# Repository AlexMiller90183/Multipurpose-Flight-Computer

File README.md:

Multipurpose Flight Computer
============================
This project is a flight computer designed to be used for many purposes, whether it be RC airplanes, model rockets, or even drones. Because of the broad usage capability it's designed to be as small as possible. It includes a barometer, IMU, servo outputs, and a battery controller. It is all powered by the STM32

PCB:
====
Schematic:

Why this?
=========
Well there I was... sitting bored at home

Just kidding. I previously made an Arduino Nano based flight computer with premade components and it was my first ever PCB! As I've learned more though, I wanted to challenge myself with something a little more complex and this was the perfect idea! I followed @NotARoomba's tutorial, but tried to make my version as small and compact as possible.

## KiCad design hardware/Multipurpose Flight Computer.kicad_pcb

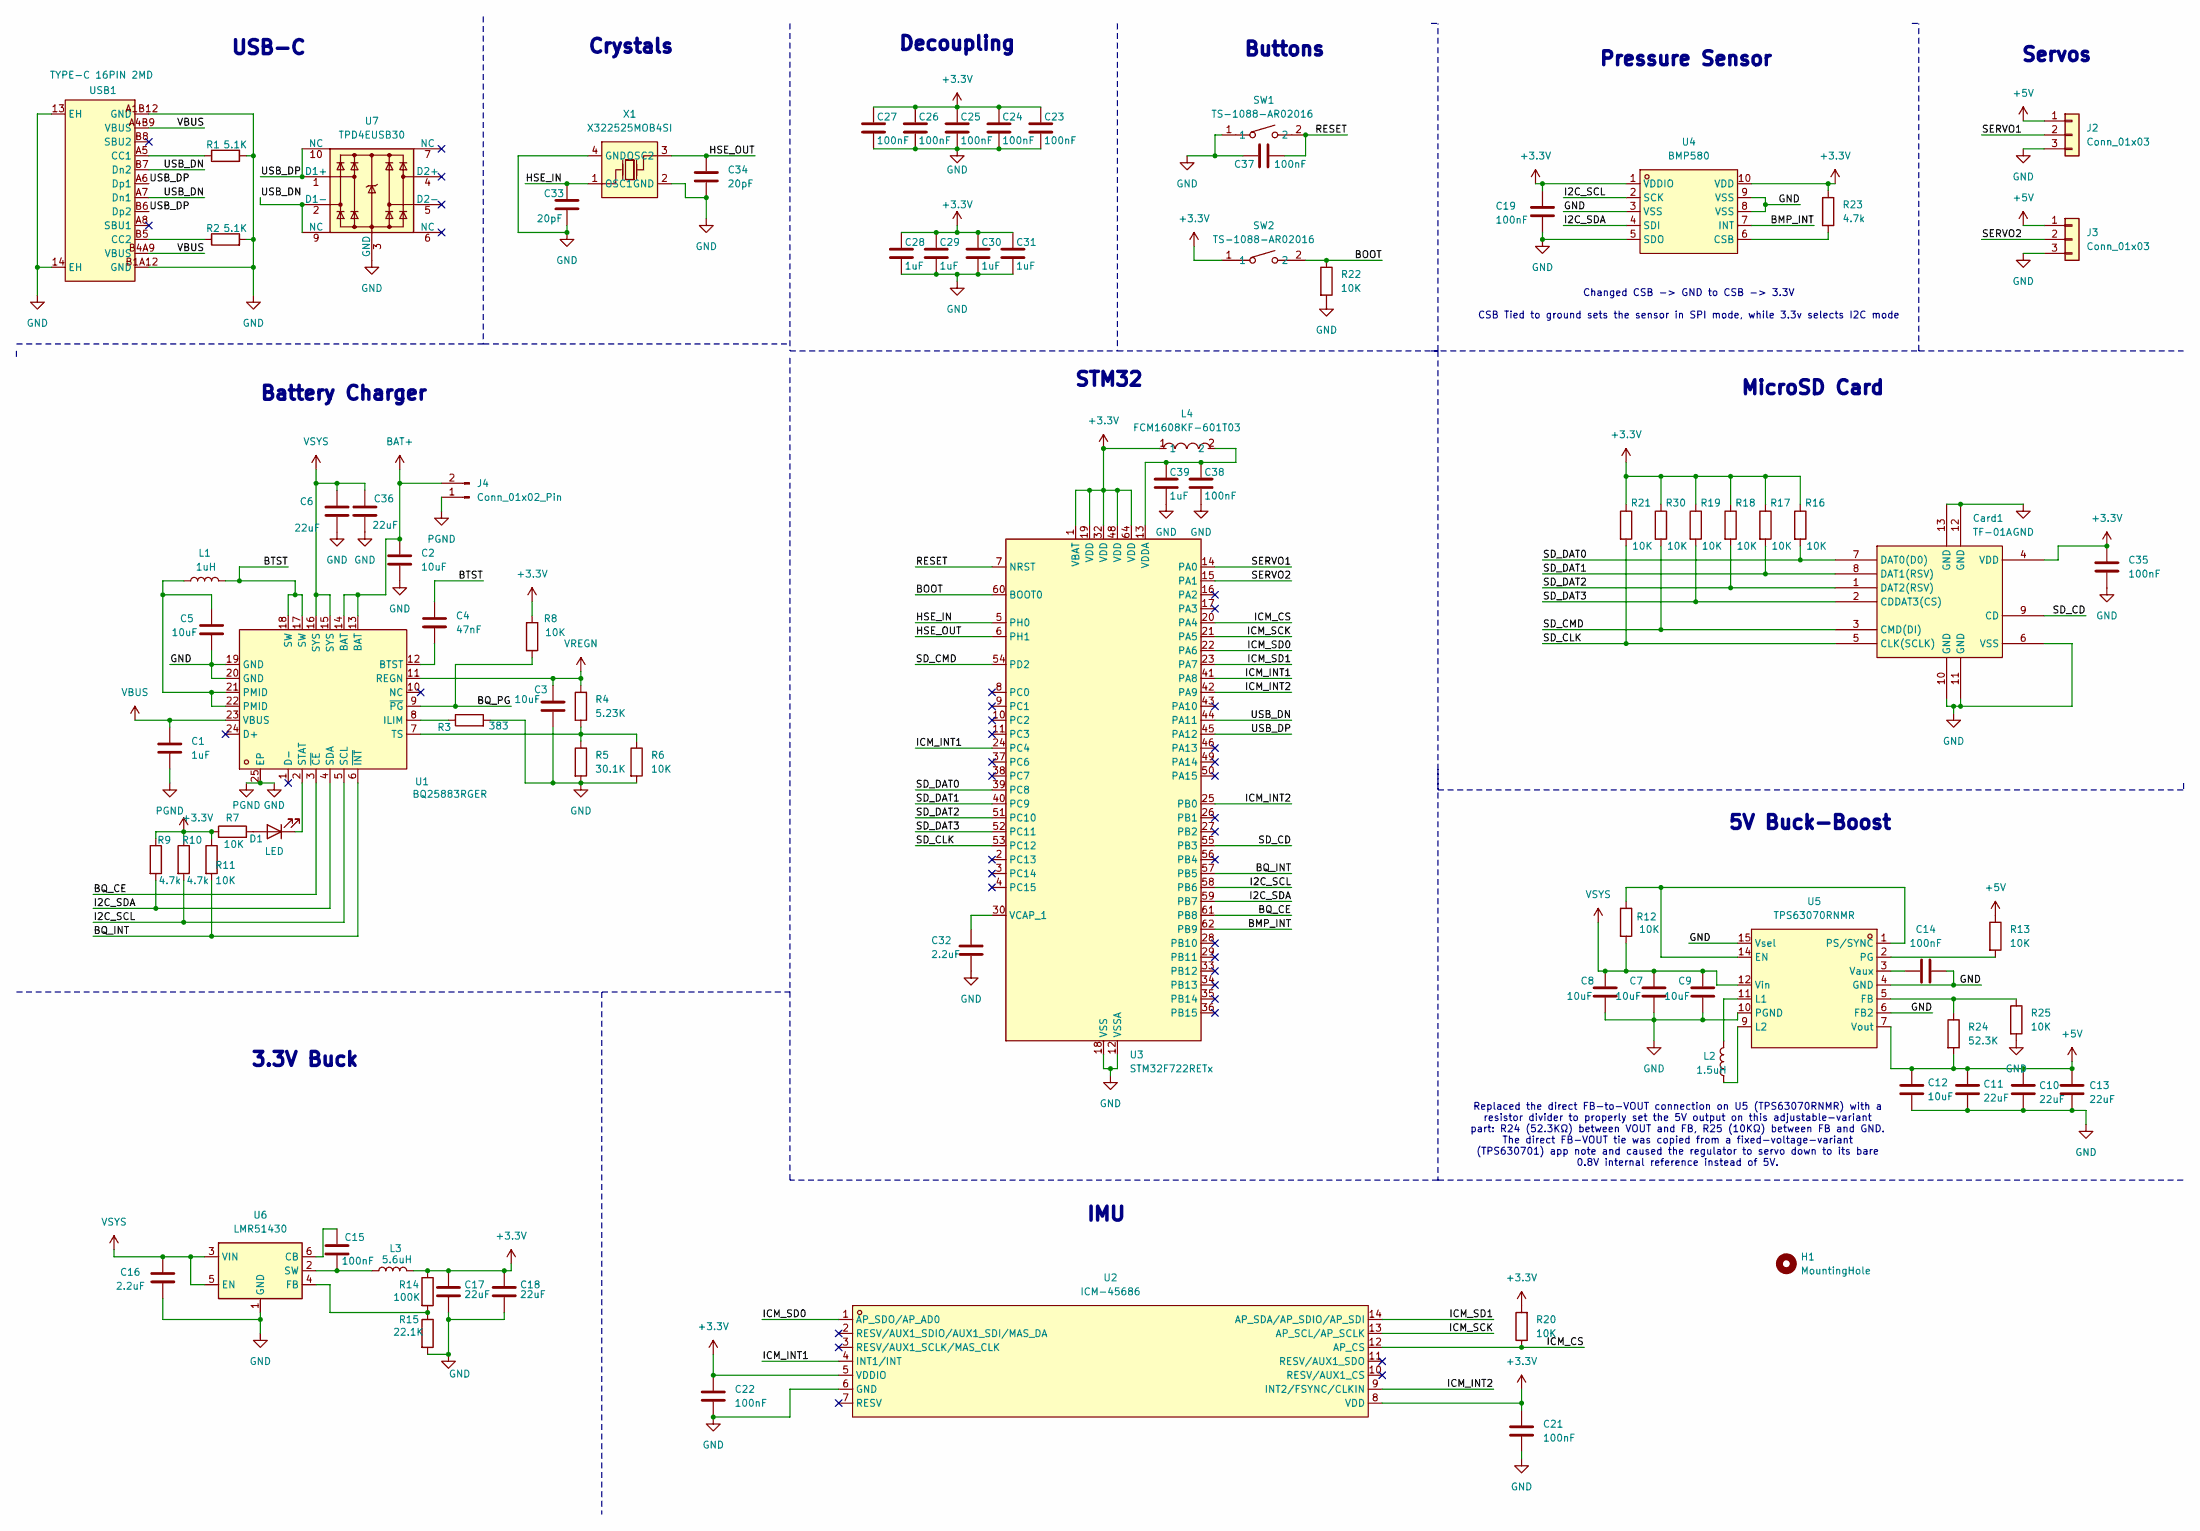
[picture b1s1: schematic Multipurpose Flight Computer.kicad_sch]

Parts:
C1, C28, C29, C30, C31, C39: 1uF; C_0402_1005Metric
C2, C12: 10uF; C_0603_1608Metric
C3, C5: 10uF; C_0402_1005Metric
C4: 47nF; C_0201_0603Metric
C6, C36: 22uF; C_0603_1608Metric
C7, C8, C9: 10uF; C_0805_2012Metric
C10, C11, C13: 22uF; C_0805_2012Metric
C14, C15, C19, C21, C22, C23, C24, C25, C26, C27, C35, C37, C38: 100nF; C_0201_0603Metric
C16: 2.2uF; C_0603_1608Metric
C17, C18: 22uF; C_0402_1005Metric
C32: 2.2uF; C_0201_0603Metric
C33, C34: 20pF; C_0201_0603Metric
Card1: TF-01A; TF-SMD_TF-01A; MPN TF-01A; LCSC Part C91145
D1: LED; LED_0402_1005Metric
H1: MountingHole; MountingHole_2.2mm_M2_DIN965_Pad_TopBottom
J2, J3: Conn_01x03; PinHeader_1x03_P2.54mm_Vertical
J4: Conn_01x02_Pin; CONN-TH_XT30PW-M
L1: 1uH; L2520
L2: 1.5uH; IND-SMD_L4.0-W4.0-A
L3: 5.6uH; IND-SMD_L3.0-W3.0
L4: FCM1608KF-601T03; L0603; MPN FCM1608KF-601T03; LCSC Part C141723
R1, R2: 5.1K; R_0201_0603Metric
R3: 383; R_0603_1608Metric
R4: 5.23K; R_0201_0603Metric
R5: 30.1K; R_0402_1005Metric
R6, R7, R8, R11, R12, R13, R16, R17, R18, R19, R20, R21, R22, R25, R30: 10K; R_0201_0603Metric
R9, R10, R23: 4.7k; R_0201_0603Metric
R14: 100K; R_0402_1005Metric
R15: 22.1K; R_0402_1005Metric
R24: 52.3K; R_0201_0603Metric
SW1, SW2: TS-1088-AR02016; SW-SMD_L3.9-W3.0-P4.45; MPN TS-1088-AR02016; LCSC Part C720477
U1: BQ25883RGER; VFQFPN-24_L4.0-W4.0-P0.50-BL-EP2.8; MPN BQ25883RGER; LCSC Part C544362
U2: ICM-45686; LGA-14_L3.0-W2.5-P0.50-TL; MPN ICM-45686; LCSC Part C22459454
U3: STM32F722RETx; LQFP-64_10x10mm_P0.5mm
U4: BMP580; LGA-10_L2.0-W2.0-P0.50-TL_BMP580; MPN BMP580; LCSC Part C22391138
U5: TPS63070RNMR; VQFN-15_L3.0-W2.5-P0.50-BL; MPN TPS63070RNMR; LCSC Part C109322
U6: LMR51430; SOT-23-6
U7: TPD4EUSB30; USON-10_2.5x1.0mm_P0.5mm
USB1: TYPE-C 16PIN 2MD; USB-C-SMD_TYPE-C-16PIN-2MD-073; MPN TYPE-C 16PIN 2MD(073); LCSC Part C2765186
X1: X322525MOB4SI; CRYSTAL-SMD_4P-L3.2-W2.5-BL; MPN X322525MOB4SI; LCSC Part C9006

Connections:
+3.3V: C17.1, C18.1, C19.1, C21.1, C22.1, C23.1, C24.1, C25.1, C26.1, C27.1, C28.1, C29.1, C30.1, C31.1, C35.2, Card1.4 (VDD), L3.2, L4.1, R7.1, R8.1, R9.1, R10.1, R11.1, R14.1, R16.1, R17.1, R18.1, R19.1, R20.2, R21.1, R23.1, R30.1, SW2.1, U2.5 (VDDIO), U2.8 (VDD), U3.1 (VBAT), U3.19 (VDD), U3.32 (VDD), U3.48 (VDD), U3.64 (VDD), U4.1 (VDDIO), U4.10 (VDD)
+5V: C10.1, C11.1, C12.1, C13.1, J2.1, J3.1, R13.1, R24.2, U5.7 (Vout)
/BMP_INT: U3.62 (PB9), U4.7 (INT)
/BOOT: R22.1, SW2.2, U3.60 (BOOT0)
/BQ_CE: U1.3 (~CE), U3.61 (PB8)
/BQ_INT: R11.2, U1.6 (~INT), U3.57 (PB5)
/BQ_PG: R8.2, U1.9 (~PG)
/BTST: C4.1, L1.2, U1.17 (SW), U1.18 (SW)
/HSE_IN: C33.1, U3.5 (PH0), X1.1 (OSC1)
/HSE_OUT: C34.1, U3.6 (PH1), X1.3 (OSC2)
/I2C_SCL: R10.2, U1.5 (SCL), U3.58 (PB6), U4.2 (SCK)
/I2C_SDA: R9.2, U1.4 (SDA), U3.59 (PB7), U4.4 (SDI)
/ICM_CS: R20.1, U2.12 (AP_CS), U3.20 (PA4)
/ICM_INT1: U2.4 (INT1/INT), U3.24 (PC4), U3.41 (PA8)
/ICM_INT2: U2.9 (INT2/FSYNC/CLKIN), U3.25 (PB0), U3.42 (PA9)
/ICM_SCK: U2.13 (AP_SCL/AP_SCLK), U3.21 (PA5)
/ICM_SD0: U2.1 (AP_SDO/AP_AD0), U3.22 (PA6)
/ICM_SD1: U2.14 (AP_SDA/AP_SDIO/AP_SDI), U3.23 (PA7)
/RESET: C37.1, SW1.2, U3.7 (NRST)
/SD_CD: Card1.9 (CD), U3.55 (PB3)
/SD_CLK: Card1.5 (CLK(SCLK)), R21.2, U3.53 (PC12)
/SD_CMD: Card1.3 (CMD(DI)), R30.2, U3.54 (PD2)
/SD_DAT0: Card1.7 (DAT0(D0)), R16.2, U3.39 (PC8)
/SD_DAT1: Card1.8 (DAT1(RSV)), R17.2, U3.40 (PC9)
/SD_DAT2: Card1.1 (DAT2(RSV)), R18.2, U3.51 (PC10)
/SD_DAT3: Card1.2 (CDDAT3(CS)), R19.2, U3.52 (PC11)
/SERVO1: J2.2, U3.14 (PA0)
/SERVO2: J3.2, U3.15 (PA1)
/USB_DN: U3.44 (PA11), U7.2 (D1-), U7.9 (NC), USB1.A7 (Dn1), USB1.B7 (Dn2)
/USB_DP: U3.45 (PA12), U7.1 (D1+), U7.10 (NC), USB1.A6 (Dp1), USB1.B6 (Dp2)
BAT+: C2.1, J4.2, U1.13 (BAT), U1.14 (BAT)
GND: C1.2, C2.2, C3.2, C5.2, C6.2, C7.2, C8.2, C9.2, C10.2, C11.2, C12.2, C13.2, C14.2, C16.2, C17.2, C18.2, C19.2, C21.2, C22.2, C23.2, C24.2, C25.2, C26.2, C27.2, C28.2, C29.2, C30.2, C31.2, C32.2, C33.2, C34.2, C35.1, C36.2, C37.2, C38.2, C39.2, Card1.6 (VSS), Card1.10 (GND), Card1.11 (GND), Card1.12 (GND), Card1.13 (GND), J2.3, J3.3, J4.1, R1.2, R2.2, R3.2, R5.2, R6.2, R15.2, R22.2, R25.2, SW1.1, U1.19 (GND), U1.20 (GND), U1.25 (EP), U2.6 (GND), U3.12 (VSSA), U3.18 (VSS), U3.31 (VSS), U3.47 (VSS), U3.63 (VSS), U4.3 (VSS), U4.5 (SDO), U4.8 (VSS), U4.9 (VSS), U5.4 (GND), U5.6 (FB2), U5.10 (PGND), U5.15 (Vsel), U6.1 (GND), U7.3 (GND), U7.8 (GND), USB1.13 (EH), USB1.14 (EH), USB1.A1B12 (GND), USB1.B1A12 (GND), X1.2 (GND), X1.4 (GND)
unnamed: C5.1, L1.1, U1.21 (PMID), U1.22 (PMID)
unnamed: D1.2 (A), R7.2
unnamed: D1.1 (K), U1.2 (STAT)
unnamed: C4.2, U1.12 (BTST)
unnamed: R3.1, U1.8 (ILIM)
unnamed: R4.2, R5.1, R6.1, U1.7 (TS)
unnamed: C32.1, U3.30 (VCAP_1)
unnamed: C38.1, C39.1, L4.2, U3.13 (VDDA)
unnamed: R23.2, U4.6 (CSB)
unnamed: R12.1, U5.1 (PS/SYNC), U5.14 (EN)
unnamed: R24.1, R25.1, U5.5 (FB)
unnamed: L2.2, U5.11 (L1)
unnamed: L2.1, U5.9 (L2)
unnamed: R13.2, U5.2 (PG)
unnamed: C14.1, U5.3 (Vaux)
unnamed: C15.1, U6.6 (CB)
unnamed: R14.2, R15.1, U6.4 (FB)
unnamed: C15.2, L3.1, U6.2 (SW)
unnamed: R1.1, USB1.A5 (CC1)
unnamed: R2.1, USB1.B5 (CC2)
VBUS: C1.1, U1.23 (VBUS), USB1.A4B9 (VBUS), USB1.B4A9 (VBUS)
VREGN: C3.1, R4.1, U1.11 (REGN)
VSYS: C6.1, C7.1, C8.1, C9.1, C16.1, C36.1, R12.2, U1.15 (SYS), U1.16 (SYS), U5.12 (Vin), U6.3 (VIN), U6.5 (EN)

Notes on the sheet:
STM32
Crystals
3.3V Buck
USB-C
Replaced the direct FB-to-VOUT connection on U5 (TPS63070RNMR) with a resistor divider to properly set the 5V output on this adjustable-variant part: R24 (52.3KΩ) between VOUT and FB, R25 (10KΩ) between FB and GND. The direct FB-VOUT tie was copied from a fixed-voltage-variant (TPS630701) app note 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
IMU
MicroSD Card
Servos
Decoupling
Battery Charger
Buttons
5V Buck-Boost
Changed CSB -> GND to CSB -> 3.3V CSB Tied to ground sets the sensor in SPI mode, while 3.3v selects I2C mode
Pressure Sensor

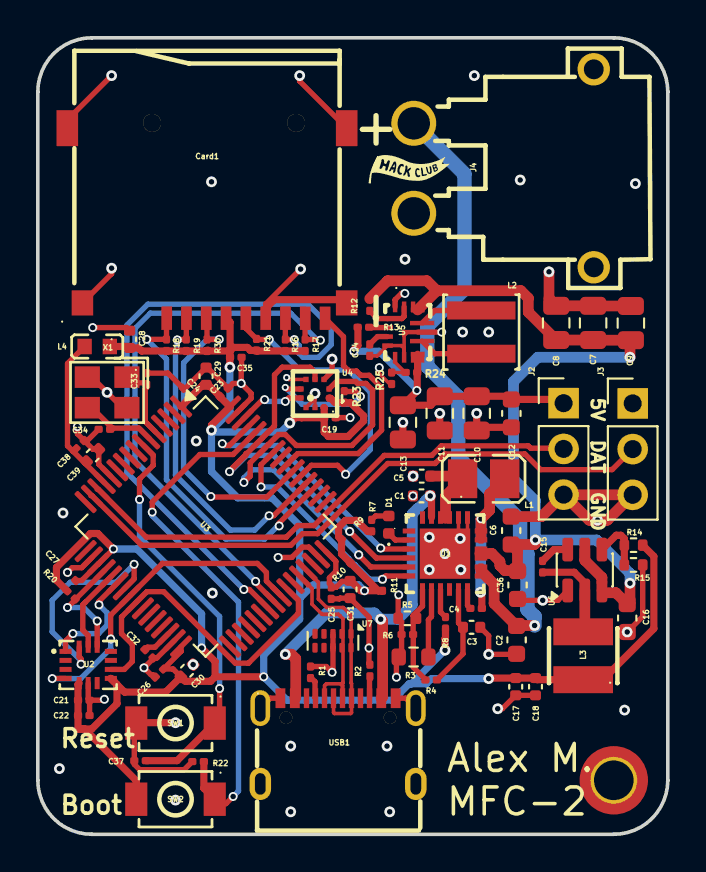
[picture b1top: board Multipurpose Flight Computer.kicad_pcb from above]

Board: 4 copper layers, 35.0 x 44.3 mm, 85 parts (0 on the bottom side), 55 nets.

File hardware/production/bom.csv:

Designator,Footprint,Quantity,Value,LCSC Part #
"C1, C28, C29, C30, C31, C39",0402,6,1uF,
"C10, C11, C13",0805,3,22uF,
"C12, C2, C9",0603,3,10uF,
"C14, C15, C19, C20, C21, C22, C23, C24, C25, C26, C27, C37, C38",0201,13,100nF,
C16,0603,1,2.2uF,
"C17, C18",0402,2,22uF,
"C3, C5",0402,2,10uF,
C32,0201,1,2.2uF,
"C33, C34",0201,2,20pF,
"C35, C36",0201,2,6.8pF,
C4,0201,1,47nF,
C6,0603,1,44uF,
"C7, C8",0805,2,10uF,
CARD1,TF-SMD_TF-01A,1,TF-01A,C91145
D1,0402,1,LED,
J1,TerminalBlock_Xinya_XY308-2.54-2P_1x02_P2.54mm_Horizontal,1,Screw_Terminal_01x02,
"J2, J3",PinHeader_1x03_P2.54mm_Vertical,2,Conn_01x03,
L1,L2520,1,1uH,C435392
L2,IND-SMD_L4.0-W4.0-A,1,1.5uH,C3033018
L3,IND-SMD_L3.0-W3.0,1,5.6uH,C18236327
L4,L0603,1,FCM1608KF-601T03,C141723
"R1, R2",0201,2,5.1K,
"R10, R11, R12, R13, R16, R17, R18, R19, R21, R22, R30, R6, R7, R8, R9",0201,15,10K,
R14,0402,1,100K,
R15,0402,1,22.1K,
R3,0201,1,3B3,
R4,0201,1,5.23K,
R5,0201,1,30.1K,
"SW1, SW2",SW-SMD_L3.9-W3.0-P4.45,2,TS-1088-AR02016,C720477
U1,VFQFPN-24_L4.0-W4.0-P0.50-BL-EP2.8,1,BQ25883RGER,C544362
U2,LGA-14_L3.0-W2.5-P0.50-TL,1,ICM-45686,C22459454
U3,LQFP-64_10x10mm_P0.5mm,1,STM32F722RETx,
U4,LGA-10_L2.0-W2.0-P0.50-TL_BMP580,1,BMP580,C22391138
U5,VQFN-15_L3.0-W2.5-P0.50-BL,1,TPS63070RNMR,C109322
U6,SOT-23-6,1,LMR51430,
U7,USON-10_2.5x1.0mm_P0.5mm,1,TPD4EUSB30,
USB1,USB-C-SMD_TYPE-C-16PIN-2MD-073,1,TYPE-C 16PIN 2MD,C2765186
X1,CRYSTAL-SMD_4P-L3.2-W2.5-BL,1,X322525MOB4SI,C9006
X2,FC-135R_L3.2-W1.5,1,Q13FC1350000400,C32346

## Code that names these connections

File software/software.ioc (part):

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Mcu.Name=STM32F722R(C-E)Tx
Mcu.Package=LQFP64
Mcu.UserName=STM32F722RETx
PA0-WKUP.Signal=GPIO_Output
PA1.Signal=S_TIM2_CH2
PA11.Mode=Device_Only
PA11.Signal=USB_OTG_FS_DM
PA12.Mode=Device_Only
PA12.Signal=USB_OTG_FS_DP
PA4.Signal=GPIO_Output
PA5.Mode=Full_Duplex_Master
PA5.Signal=SPI1_SCK
PA6.Mode=Full_Duplex_Master
PA6.Signal=SPI1_MISO
PA7.Mode=Full_Duplex_Master
PA7.Signal=SPI1_MOSI
PB0.GPIOParameters=GPIO_Label
PB0.GPIO_Label=ICM_INT2
PB0.Signal=GPXTI0
PB3.GPIOParameters=GPIO_Label
PB3.GPIO_Label=SD_CS
PB3.Signal=GPIO_Input
PB5.GPIOParameters=GPIO_Label
PB5.GPIO_Label=BQ_INT
PB5.Signal=GPXTI5
PB6.Mode=I2C
PB6.Signal=I2C1_SCL
PB7.Mode=I2C
PB7.Signal=I2C1_SDA
PB8.GPIOParameters=GPIO_Label
PB8.GPIO_Label=BQ_CE
PB8.Signal=GPIO_Output
PB9.GPIOParameters=GPIO_Label
PB9.GPIO_Label=BMP_INT
PB9.Signal=GPXTI9
PC10.Mode=SD_4_bits_Wide_bus
PC10.Signal=SDMMC1_D2
PC11.Mode=SD_4_bits_Wide_bus
PC11.Signal=SDMMC1_D3
PC12.Mode=SD_4_bits_Wide_bus
PC12.Signal=SDMMC1_CK
PC14-OSC32_IN.Mode=LSE-External-Oscillator
PC14-OSC32_IN.Signal=RCC_OSC32_IN
PC15-OSC32_OUT.Mode=LSE-External-Oscillator
PC15-OSC32_OUT.Signal=RCC_OSC32_OUT
PC4.GPIOParameters=GPIO_Label
PC4.GPIO_Label=ICM_INT1
PC4.Signal=GPXTI4
PC8.Mode=SD_4_bits_Wide_bus
PC8.Signal=SDMMC1_D0
PC9.Mode=SD_4_bits_Wide_bus
PC9.Signal=SDMMC1_D1
PD2.Mode=SD_4_bits_Wide_bus
PD2.Signal=SDMMC1_CMD
PH0-OSC_IN.Mode=HSE-External-Oscillator
PH0-OSC_IN.Signal=RCC_OSC_IN
PH1-OSC_OUT.Mode=HSE-External-Oscillator
PH1-OSC_OUT.Signal=RCC_OSC_OUT
RCC.HSE_VALUE=25000000
RCC.SYSCLKFreq_VALUE=40000000
RCC.SYSCLKSource=RCC_SYSCLKSOURCE_PLLCLK
board=custom
